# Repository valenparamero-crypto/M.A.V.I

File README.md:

<div align="center">

# 🤖 M.A.V.I.
### Módulo Autónomo de Visión Inteligente

*Vehículo Guiado Automáticamente (AGV) con plataforma holonómica y visión artificial*

**Universidad Tecnológica de Pereira** · Facultad de Tecnología
Ingeniería Mecatrónica · Semestre Integrador 2026-2 · **Grupo 2**

[Introducción](#-introducción) ·
[Objetivo](#-objetivo-general) ·
[Áreas](#-áreas-de-desarrollo) ·
[Materiales](#-materiales-y-tecnologías) ·
[Estado](#-estado-actual) ·
[Equipo](#-equipo)

</div>

---

## 📌 Introducción

**M.A.V.I.** es un AGV diseñado para el transporte interno de cargas de hasta **1 kg** entre estaciones de carga y descarga, sobre una pista compartida con otros equipos. El vehículo sigue la pista con una cámara, reconoce cada estación mediante **AprilTags**, detecta si lleva carga, identifica obstáculos y se comunica con las estaciones por infrarrojo. Además, cuenta con una interfaz de usuario para supervisar el vehículo, asignar misiones y detenerlo a distancia.

El proyecto se construye sobre cuatro áreas:

| | Área | En pocas palabras |
| :---: | :--- | :--- |
| 🔧 | **Diseño mecánico** | Chasis impreso en PLA, inspirado en robots logísticos tipo Amazon Kiva, con 2 ruedas Mecanum de tracción diferencial y 4 ruedas locas de apoyo. |
| ⚡ | **Electrónica y potencia** | Batería LiPo de 7.4 V, regulación a 5.1 V con un XL4016 y una PCB propia que integra potencia, driver de motores y sensores. |
| 🎛️ | **Control y movimiento** | Una ESP32-S3 controla los motores con encoders y lee los sensores: IMU, distancia láser, báscula, infrarrojo y paro de emergencia. |
| 👁️ | **Visión por computador** | Una Raspberry Pi 5 con cámara gran angular de 162° detecta la pista, los AprilTags y los obstáculos, y envía las órdenes a la ESP32-S3 por I²C. |

<div align="center">

```text
 Cámara IMX219 ──► Raspberry Pi 5 ──I²C──► ESP32-S3 ──► TB6612FNG ──► Motores JGY-370
  (visión)         (decisiones)           (control)      (driver)       (con encoder)
                                             ▲
               BMI270 · VL53L1X · HX711 · Infrarrojo · Paro de emergencia
```

</div>

---

## 🎯 Objetivo general

Desarrollar un vehículo guiado automáticamente (AGV) que integre una plataforma holonómica y visión artificial, con capacidad para transportar cargas de hasta 1 kg entre estaciones predefinidas de carga y descarga en una pista compartida, antes de finalizar el semestre académico 2026-2.

---

## 📂 Áreas de desarrollo

Cada área tiene su propia carpeta con un README que explica su contenido en detalle.

| Carpeta | Qué contiene |
| :--- | :--- |
| 📄 [**documentación**](documentación/) | Acta de constitución, propuesta formal, cronograma (Gantt), ruta crítica (CPM) y bitácoras de planeación y ejecución. |
| ⚡ [**diseño electrónico**](diseño%20electrónico/) | Diagrama de bloques, esquema electrónico, diseño de la PCB y evidencias de pruebas. |
| 🔧 [**diseño mecánico**](diseño%20mecánico/) | Modelos CAD del chasis (versión inicial y modelo integral), listado de materiales y evidencias de fabricación. |
| 💻 [**src**](src/) | Código fuente: firmware de la ESP32-S3 (C++), programas de la Raspberry Pi 5 (Python) y el protocolo I²C compartido. |

---

## 🧰 Materiales y tecnologías

<details>
<summary><b>⚡ Materiales electrónicos</b> (clic para ver)</summary>
<br>

| Componente | Descripción | Función |
| :--- | :--- | :--- |
| Raspberry Pi 5 (8 GB) | Computador de placa única | Visión artificial y toma de decisiones |
| Cámara IMX219-160 | 8 MP, 162° de campo de visión, conexión CSI | Captura de la pista, AprilTags y obstáculos |
| ESP32-S3 N16R8 | Microcontrolador de doble núcleo | Control de motores y lectura de sensores |
| TB6612FNG | Driver de motores (puente H doble) | Controla velocidad y sentido de giro |
| Motorreductor JGY-370 (x2) | 6 V, 100 RPM, con encoder | Tracción y medición del giro de las ruedas |
| Batería LiPo 7.4 V 5000 mAh | Batería de litio-polímero 2S | Alimentación de todo el sistema |
| XL4016 | Convertidor DC-DC reductor | Baja de 7.4 V a 5.1 V para la electrónica |
| BMI270 | Unidad de medición inercial (SPI) | Mide giros y aceleraciones |
| VL53L1X (módulo TOF400C) | Sensor láser de distancia (hasta 4 m) | Mide la distancia a obstáculos |
| Celda de carga 3 kg + HX711 | Sensor de peso y conversor A/D | Detecta si hay carga sobre el vehículo |
| Par infrarrojo | Emisor y receptor IR | Comunicación con las estaciones |
| Pulsador de emergencia | Pulsador normalmente abierto | Detiene los motores ante un riesgo |
| Ventilador 5 V | Ventilador pequeño | Enfría el regulador |
| PCB M.A.V.I. | Placa de circuito impreso propia | Integra potencia y conexiones de señal |

</details>

<details>
<summary><b>🔧 Materiales mecánicos</b> (clic para ver)</summary>
<br>

| Componente | Material | Método de fabricación | Observaciones |
| :--- | :--- | :--- | :--- |
| Chasis final | PLA | Impresión 3D (filamento) | Modelo integral diseñado en Fusion 360 |
| Chasis de pruebas | MDF | Corte láser | Validación de medidas y montaje |
| Soportes de motores | PLA / resina | Impresión 3D | Fijan los motores al chasis |
| Acoples de rueda | Resina | Impresión 3D | Unen el eje del motor con la rueda Mecanum |
| Soportes de ruedas locas | PLA | Impresión 3D | Cuatro puntos de apoyo |
| Ruedas Mecanum 60 mm (x2) | Comercial | Compradas | Rodillos a 45° |
| Ruedas locas (x4) | Comercial | Compradas | Estabilidad del vehículo |

</details>

<details>
<summary><b>🛠️ Herramientas utilizadas</b> (clic para ver)</summary>
<br>

| Herramienta | Tipo | Función principal |
| :--- | :--- | :--- |
| Autodesk Fusion 360 | Software CAD / diseño electrónico | Diseño del chasis, piezas y PCB |
| Arduino IDE | Entorno de programación | Firmware de la ESP32-S3 en C++ |
| Python | Lenguaje de programación | Software de la Raspberry Pi 5 |
| OpenCV | Librería de visión artificial | Detección de pista, AprilTags y obstáculos |
| Visual Studio Code | Editor de código | Desarrollo y conexión remota a la Raspberry Pi 5 |
| Git y GitHub | Control de versiones | Trabajo colaborativo y trazabilidad |
| Impresora 3D | Máquina de fabricación | Chasis y piezas en PLA y resina |
| Cortadora láser | Máquina de fabricación | Piezas de prueba en MDF |
| Microsoft Word | Procesador de texto | Informe, artículo y manual de usuario |
| Microsoft PowerPoint | Presentaciones | Exposiciones del proyecto |
| Microsoft Excel | Hoja de cálculo | Cronograma (Gantt) |

</details>

---

## 📚 Asignaturas relacionadas

| Asignatura | Aporte al proyecto |
| :--- | :--- |
| Programación | Firmware en C++ y software en Python |
| Electrónica analógica y digital | Sensores, lógica de 3.3 V y buses I²C y SPI |
| Electrónica de potencia | Regulación de voltaje y control de motores |
| Inteligencia artificial | Visión por computador para navegación y detección |
| Automatización industrial | Concepto de AGV para logística interna |
| Dibujo técnico | Modelado CAD y planos del chasis |

---

## 🌱 Beneficios esperados

- Mostrar a escala cómo funciona el transporte interno automatizado en manufactura y logística.
- Integrar en un solo prototipo mecánica, electrónica, control, programación y visión artificial.
- Dejar una arquitectura modular (Raspberry Pi 5 + ESP32-S3 por I²C) que otros equipos puedan reutilizar.
- Documentar todo el proceso para que el proyecto pueda replicarse.

---

## 📊 Estado actual

| Módulo | Estado | Detalle |
| :--- | :---: | :--- |
| 🔧 Mecánico | 🟢 Finalizado | Chasis final impreso en PLA y ensamblado con ruedas Mecanum y ruedas locas. |
| ⚡ Electrónico | 🟢 Finalizado | PCB fabricada, soldada y probada en el robot. |
| 🎛️ Control y software | 🟡 En proceso | Las funciones ya se habían probado por separado. Al pasar a la PCB, la comunicación I²C falló; ya se recuperó y se está retomando la integración de todas las funciones y la interfaz de usuario. |
| 📄 Documentación | 🟡 En proceso | Acta, propuesta, Gantt, CPM y bitácoras completas; artículo y manual de usuario en desarrollo. |

<sub>🟢 Finalizado · 🟡 En proceso · 🔴 Pendiente</sub>

---

## 👥 Equipo

| Integrante | Área |
| :--- | :--- |
| **Juan Miguel Noreña** | Líder técnico · Electrónica |
| **Sara Edith Perilla** | Diseño mecánico |
| **Edwar Alfonso León** | Programación |
| **Laura Valentina Paramero** | Documentación |

### Docentes

| Docente | Asignatura |
| :--- | :--- |
| Edward Andrés González Ríos | Proyecto Integrador II |
| Carlos Andrés Rodríguez Pérez | Proyecto Integrador I |
| Angie Tatiana Rengifo Oviedo | Formación Integral |

---

## 📜 Licencia

Este proyecto se distribuye bajo la licencia **MIT**. Consulta el archivo [`LICENSE`](LICENSE) para más información.

<div align="center">
<sub>Universidad Tecnológica de Pereira · Ingeniería Mecatrónica · 2026</sub>
</div>

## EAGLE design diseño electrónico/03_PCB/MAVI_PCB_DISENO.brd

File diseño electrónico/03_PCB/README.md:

<div align="center">

# 🟩 Diseño de la PCB

Placa de circuito impreso propia de M.A.V.I., que integra en una sola tarjeta la distribución de potencia, el control de los motores y la conexión de los sensores.

**2 capas · 1.6 mm de grosor · 99.45 × 118.35 mm**

&nbsp;&nbsp;

<sub>Vista superior e inferior del modelo 3D</sub>

</div>

---

### 👁️ Visualización

 **MAVI_PCB_DISENO.pdf**

Plano de la placa en una hoja tamaño A3, en el que se superponen las dos capas de cobre: la superior en rojo y la inferior en azul. Muestra el recorrido de las pistas, la ubicación de cada componente y las serigrafías que identifican borneras, conectores y pines. Es la referencia para revisar el diseño, verificar conexiones o guiar el proceso de soldadura. Se visualiza directamente en GitHub.

 **MAVI_PCB_3D_SUPERIOR.png** · **MAVI_PCB_3D_INFERIOR.png**

Imágenes renderizadas del modelo 3D de la placa. La vista superior muestra los componentes montados: la ESP32-S3, el módulo HX711, el driver TB6612FNG, las borneras y los conectores de sensores y encoders. La vista inferior muestra la cara posterior, donde se ubican las dos resistencias del circuito. Las imágenes presentan la placa en color verde por defecto del render; la placa fabricada tiene máscara negra. Se visualizan directamente en GitHub.

---

### 🛠️ Archivos editables

 **MAVI_PCB_DISENO.fbrd**

Archivo original del diseño de la placa, creado en Autodesk Fusion 360. Contiene toda la información editable: el trazado de las pistas, las dos capas de cobre, la posición de los componentes y las reglas de diseño. Es el archivo que se debe utilizar para realizar cualquier modificación o una nueva versión de la placa. Requiere descarga y se abre con Fusion 360.

 **MAVI_PCB_DISENO.brd**

Copia del diseño de la placa exportada al formato de Autodesk Eagle, uno de los más utilizados en diseño electrónico. Su finalidad es que el diseño pueda abrirse en programas distintos a Fusion 360; por ejemplo, KiCad, software gratuito de diseño de circuitos, permite importarlo. Requiere descarga.

 **MAVI_PCB_3D.step**

Modelo tridimensional de la placa en formato STEP, el estándar para intercambiar modelos entre programas CAD. Conserva las dimensiones reales de la PCB y sus componentes, por lo que se utiliza para integrarla en el ensamble mecánico del vehículo y verificar que encaje correctamente en el chasis. Requiere descarga y se abre con Fusion 360, FreeCAD u otro software CAD.

---

<div align="center">
<sub><a href="../README.md">⬅️ Volver a Diseño electrónico</a></sub>
</div>

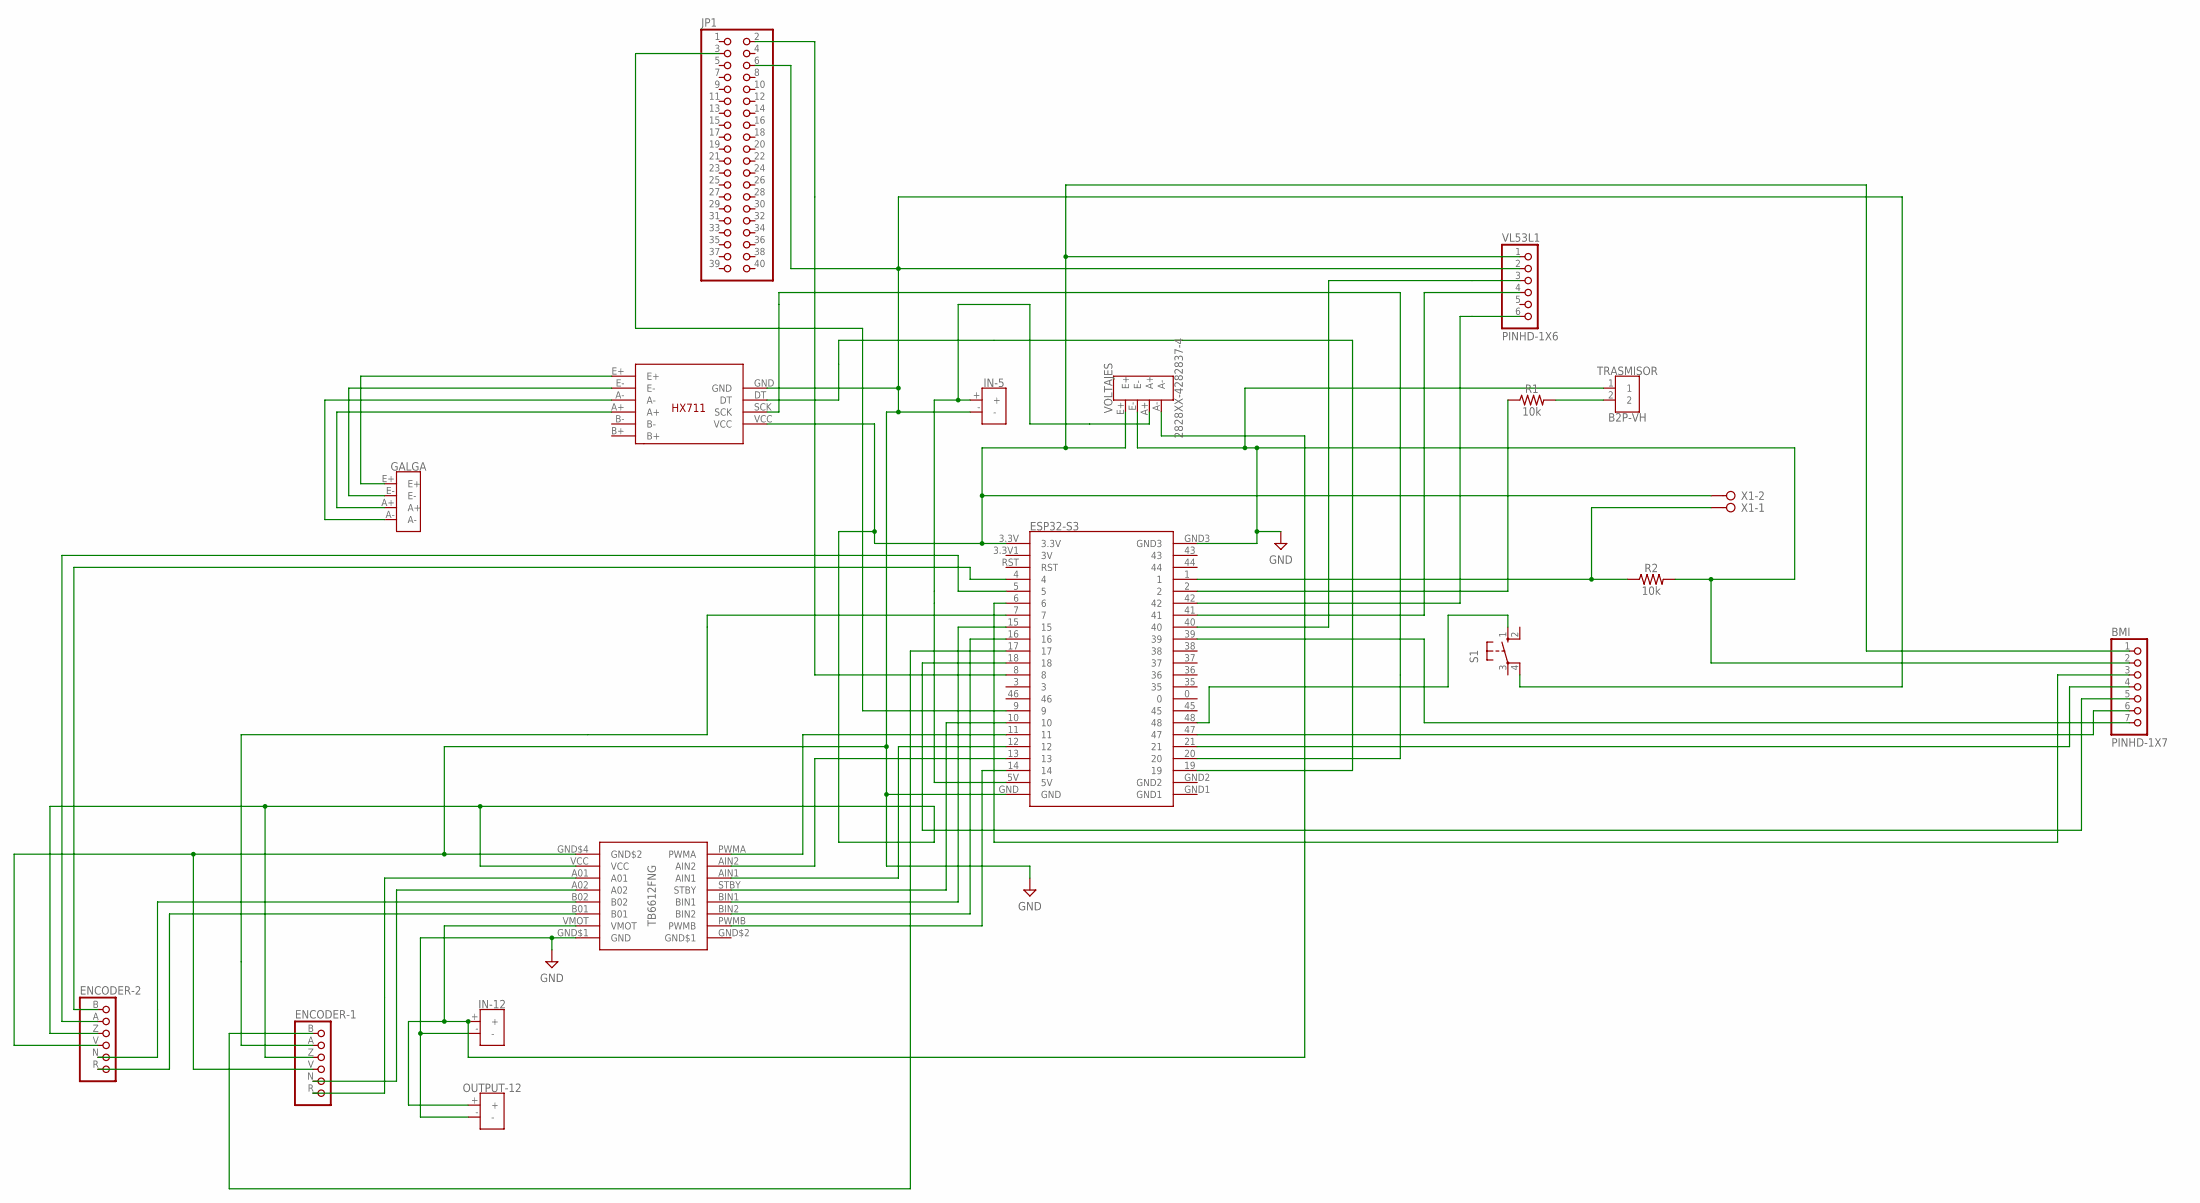
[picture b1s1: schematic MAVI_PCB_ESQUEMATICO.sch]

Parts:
BMI: PINHD-1X7; 1X07
ENCODER-1, ENCODER-2: ENCODER; 1X06
GALGA: CC282837-4; TERMBLK_508-4N
IN-5, IN-12: VOLTAJE282837-2; TERMBLK_508-2N
JP1: PINHD-2X20; 2X20
OUTPUT-12: VOLTAJE282837-2; TERMBLK_508-2N
R1, R2: 10k; AXIAL-0.3
S1: 10-XX; B3F-10XX
TRASMISOR: B2P-VH; B2P-VH_396-2N
U$1: TB6612DEFINITIVO; TB6612FNG
U$2: ESP32-S2; ESP32-S3
U$3: HX711
VL53L1: PINHD-1X6; 1X06
VOLTAJES: 2828XX-4282837-4; TERMBLK_508-4N
X1: W237-02P; W237-132

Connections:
GND: BMI.2, ENCODER-1.V, ENCODER-2.V, IN-5.-, IN-12.-, JP1.6, OUTPUT-12.-, R2.P$2 (2), S1.4 (P1), TRASMISOR.1, U$1.GND$1 (GND), U$1.GND$4 (GND$2), U$2.GND, U$2.GND3, U$3.GND, VL53L1.2, VOLTAJES.E-
unnamed: GALGA.E+, U$3.E+
unnamed: GALGA.E-, U$3.E-
unnamed: GALGA.A+, U$3.A+
unnamed: GALGA.A-, U$3.A-
unnamed: IN-12.+, OUTPUT-12.+, U$1.VMOT, VOLTAJES.A-
unnamed: BMI.1, ENCODER-1.Z, ENCODER-2.Z, U$1.VCC, U$2.3.3V, U$3.VCC, VL53L1.1, VOLTAJES.E+, X1.2
unnamed: U$2.19, U$3.DT
unnamed: ENCODER-1.R, U$1.A01
unnamed: ENCODER-1.N, U$1.A02
unnamed: ENCODER-2.N, U$1.B02
unnamed: ENCODER-2.R, U$1.B01
unnamed: U$1.PWMA, U$2.11
unnamed: U$1.AIN2, U$2.13
unnamed: U$1.AIN1, U$2.12
unnamed: U$1.STBY, U$2.10
unnamed: U$1.BIN1, U$2.15
unnamed: U$1.BIN2, U$2.16
unnamed: U$1.PWMB, U$2.14
unnamed: JP1.3, U$2.9
unnamed: JP1.2, U$2.8
unnamed: ENCODER-2.B, U$2.4
unnamed: ENCODER-2.A, U$2.5
unnamed: ENCODER-1.B, U$2.17
unnamed: ENCODER-1.A, U$2.7
unnamed: U$2.20, U$3.SCK
unnamed: U$2.40, VL53L1.3
unnamed: U$2.41, VL53L1.4
unnamed: U$2.42, VL53L1.6
unnamed: R1.P$1 (1), U$2.2
unnamed: R1.P$2 (2), TRASMISOR.2
unnamed: R2.P$1 (1), U$2.1, X1.1
unnamed: BMI.3, U$2.6
unnamed: IN-5.+, U$2.5V, VOLTAJES.A+
unnamed: BMI.4, U$2.21
unnamed: BMI.5, U$2.18
unnamed: BMI.6, U$2.47
unnamed: BMI.7, U$2.39
unnamed: S1.1 (S), U$2.48

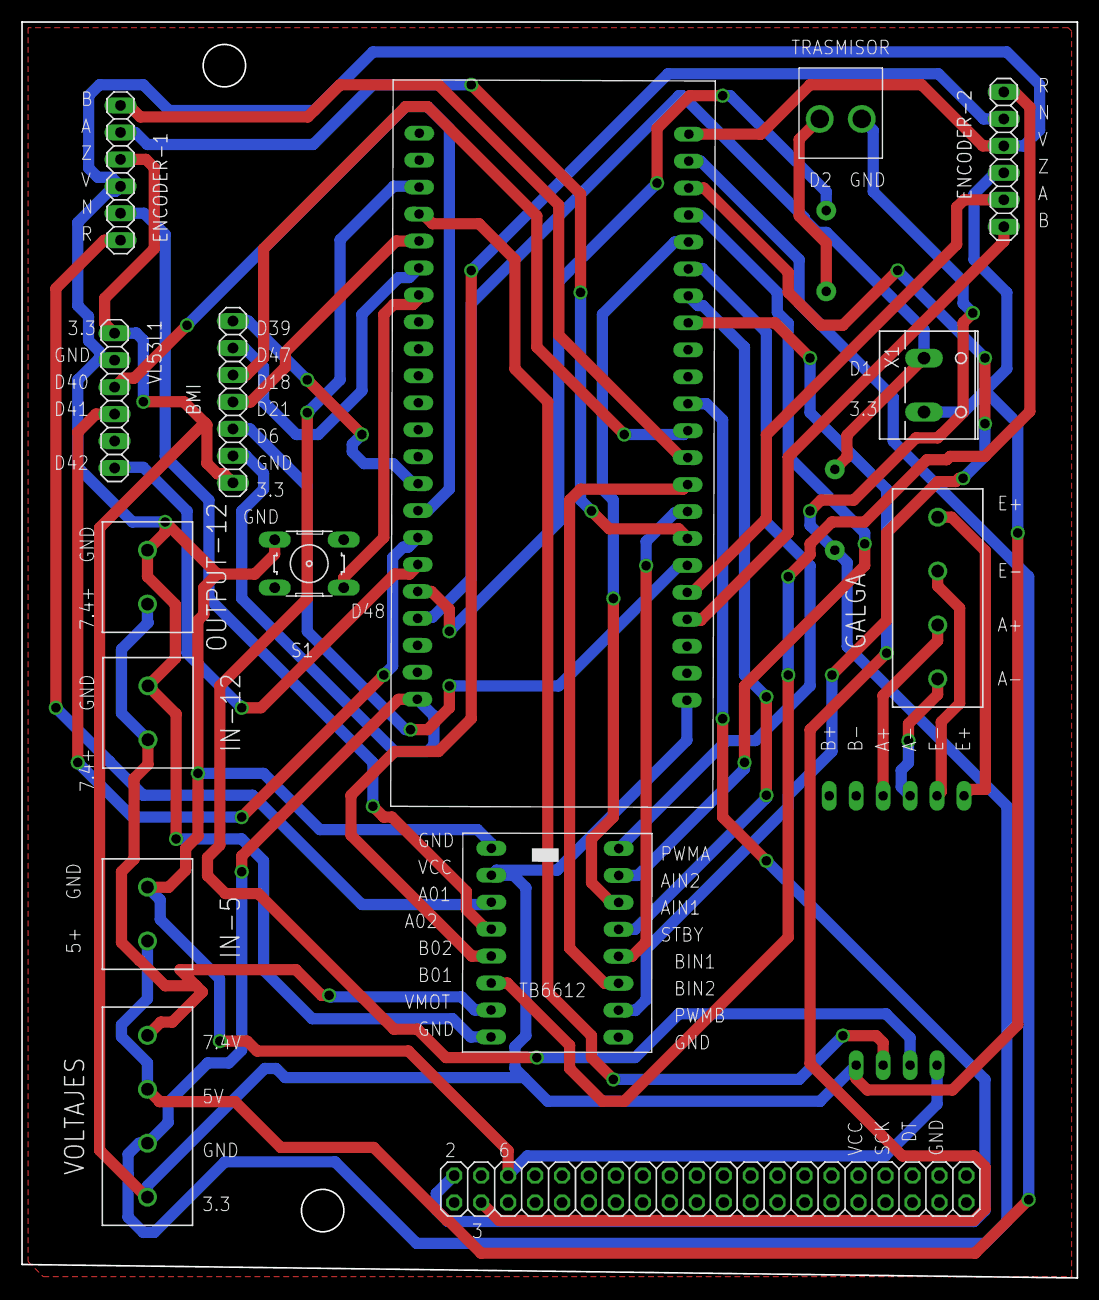
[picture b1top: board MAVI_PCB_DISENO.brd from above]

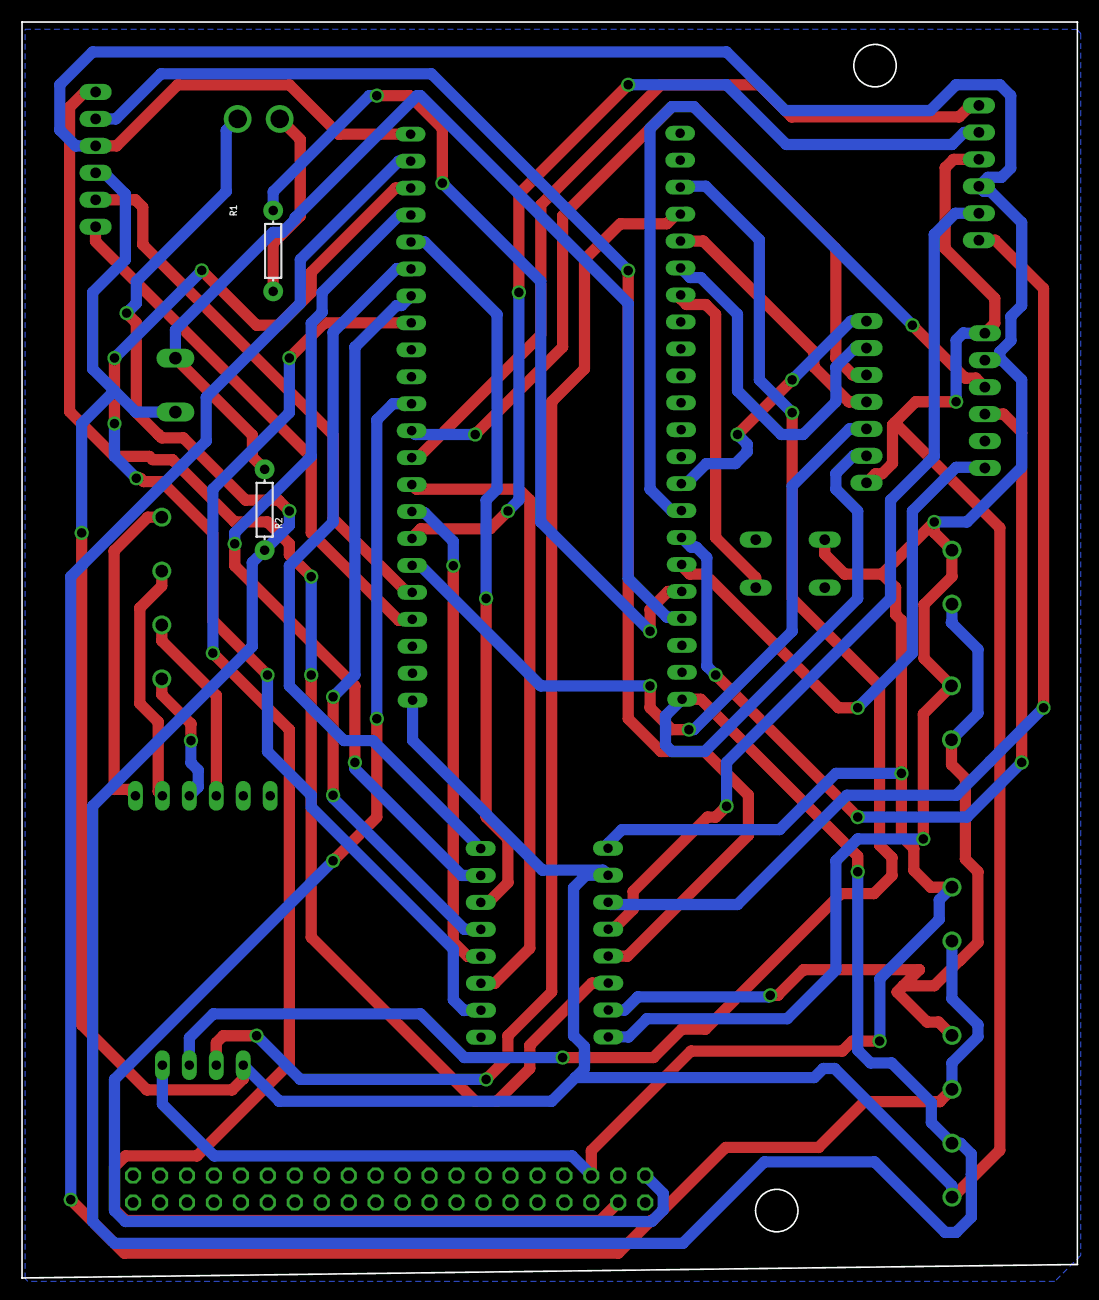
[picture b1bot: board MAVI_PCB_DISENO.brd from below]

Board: 2 copper layers, 99.5 x 118.3 mm, 18 parts (2 on the bottom side), 39 nets.

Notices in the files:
parts and their libraries:
SparkFun-Resistors: Licensing: Creative Commons ShareAlike 4.0 International - https://creativecommons.org/licenses/by-sa/4.0
